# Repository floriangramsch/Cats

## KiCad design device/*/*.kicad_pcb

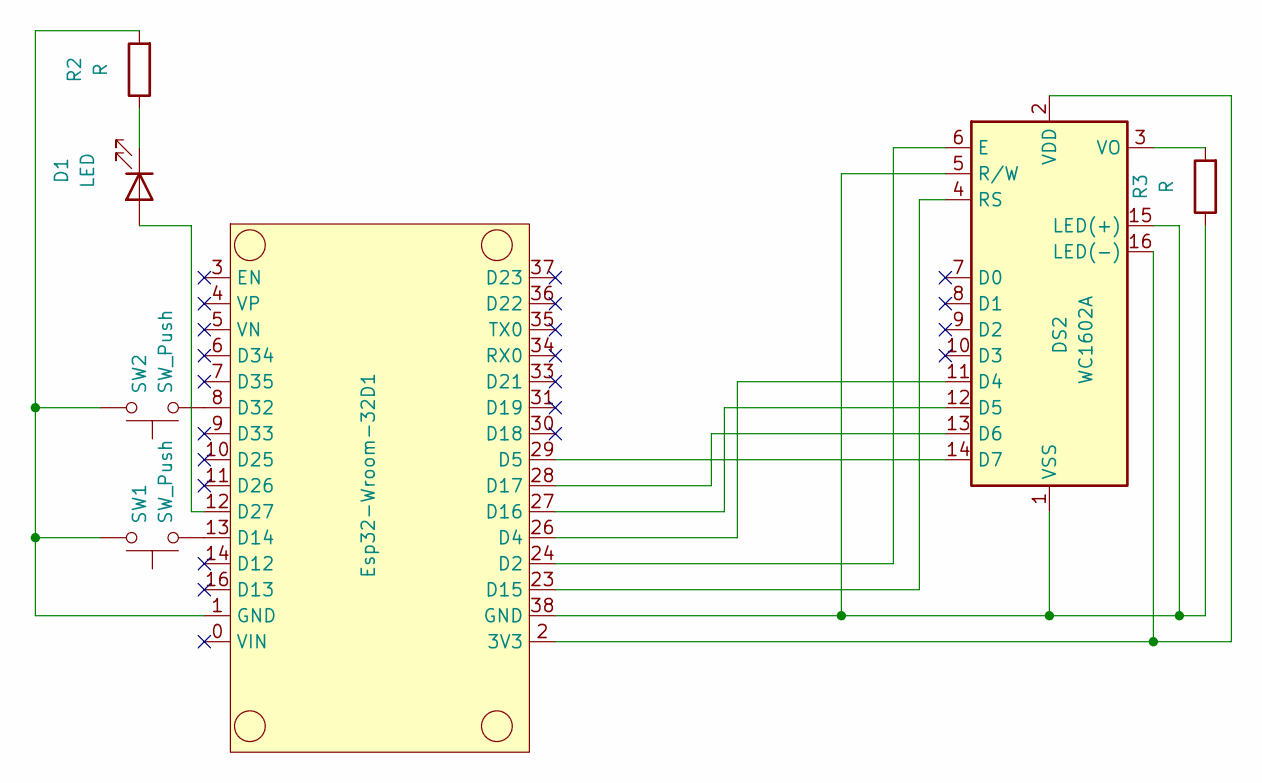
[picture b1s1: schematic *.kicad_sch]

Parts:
D1: LED; LED_D5.0mm
DS2: WC1602A
Esp32-Wroom-32D1: esp32_my_footpring
R2, R3: R; R_Axial_DIN0207_L6.3mm_D2.5mm_P7.62mm_Horizontal
SW1, SW2: SW_Push; SW_PUSH_6mm_H5mm

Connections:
unnamed: D1.2 (A), Esp32-Wroom-32D1.12 (D27)
unnamed: D1.1 (K), R2.1
unnamed: DS2.11 (D4), Esp32-Wroom-32D1.26 (D4)
unnamed: DS2.12 (D5), Esp32-Wroom-32D1.27 (D16)
unnamed: DS2.13 (D6), Esp32-Wroom-32D1.28 (D17)
unnamed: DS2.14 (D7), Esp32-Wroom-32D1.29 (D5)
unnamed: DS2.6 (E), Esp32-Wroom-32D1.24 (D2)
unnamed: DS2.1 (VSS), DS2.5 (R/W), DS2.15 (LED(+)), Esp32-Wroom-32D1.38 (GND), R3.1
unnamed: DS2.2 (VDD), DS2.16 (LED(-)), Esp32-Wroom-32D1.2 (3V3)
unnamed: DS2.4 (RS), Esp32-Wroom-32D1.23 (D15)
unnamed: DS2.3 (VO), R3.2
unnamed: Esp32-Wroom-32D1.13 (D14), SW1.1
unnamed: Esp32-Wroom-32D1.8 (D32), SW2.1
unnamed: Esp32-Wroom-32D1.1 (GND), R2.2, SW1.2, SW2.2

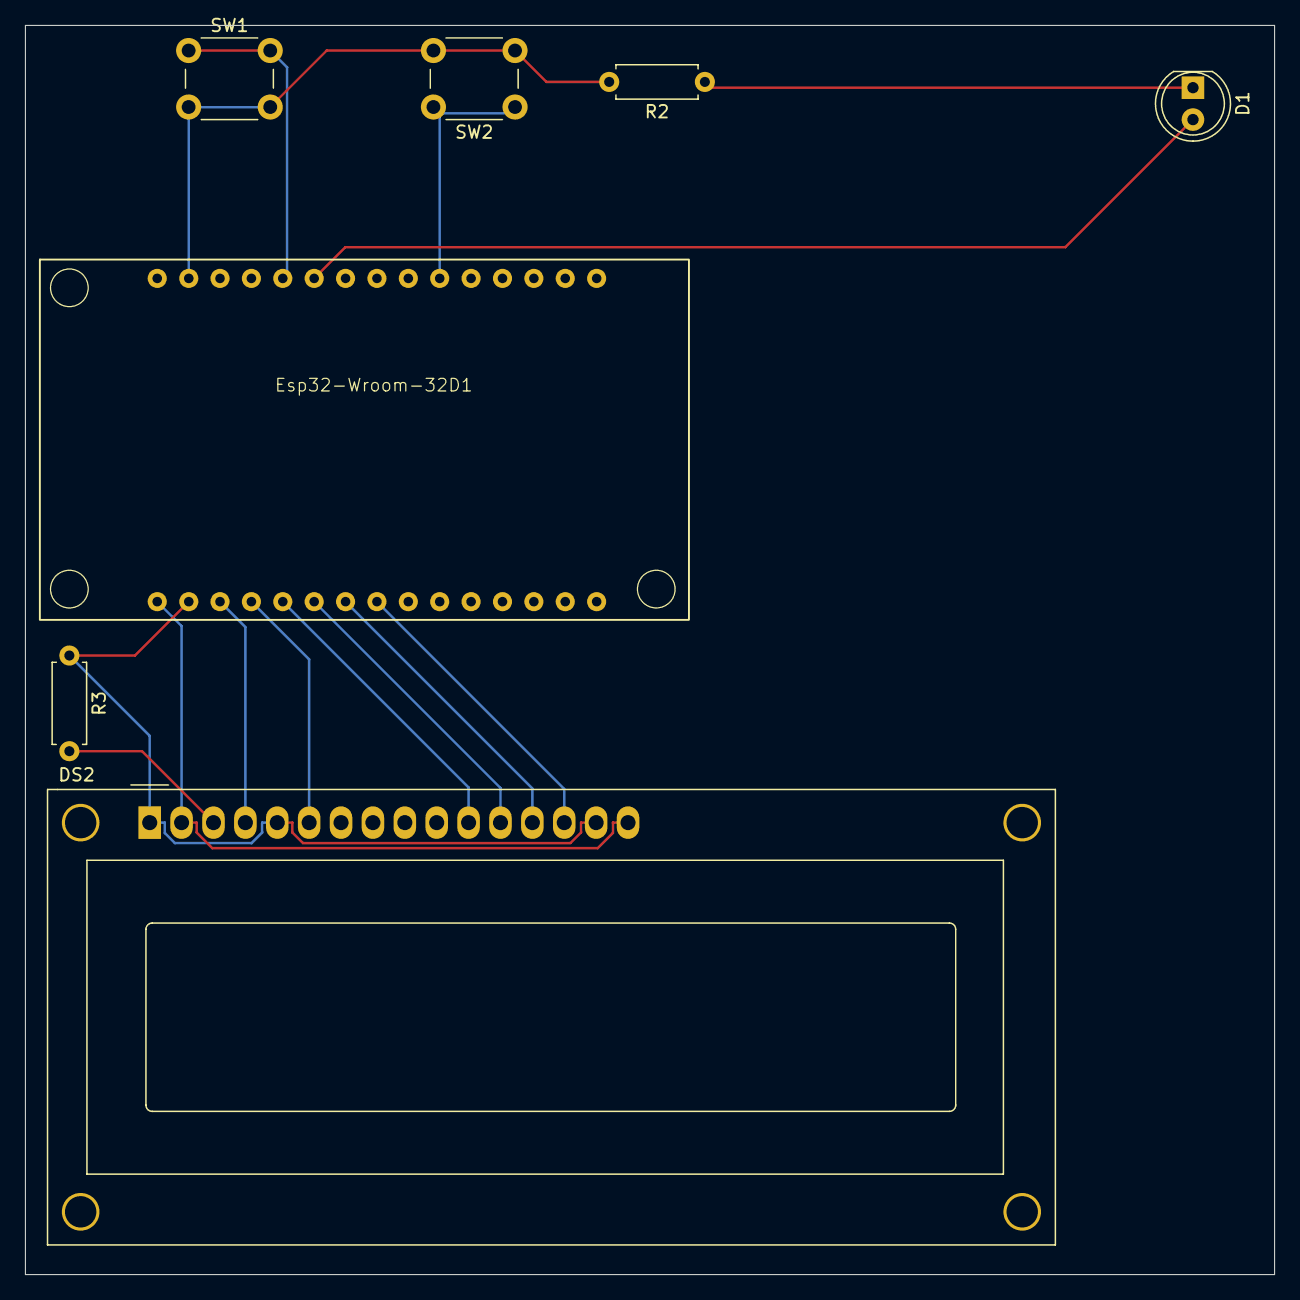
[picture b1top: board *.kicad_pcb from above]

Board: 2 copper layers, 99.5 x 99.5 mm, 7 parts (0 on the bottom side), 14 nets.

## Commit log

2024-07-11 first init
2024-07-11 another ip and no ngix
2024-07-11 Makefile
2024-07-11 ip things
2024-07-11 port
2024-07-11 dafuq alter
2024-07-11 reload page
2024-07-12 icons
2024-07-12 formatting
2024-07-12 styling
2024-07-13 second page and structure
2024-07-14 statistiken
2024-07-14 right time
2024-07-14 workflow
2024-07-14 trigger
2024-07-14 trigger workflow
2024-07-14 better label
2024-07-15 meds and kicad
2024-07-15 meds
2024-08-16 gone cats.. <3
2024-08-16 farewell
2024-11-01 new cats and better design for old cats <3
2024-11-01 fixes
2024-11-01 missing import
2024-11-01 fix import
2024-11-01 fix format
2024-11-01 better counting
